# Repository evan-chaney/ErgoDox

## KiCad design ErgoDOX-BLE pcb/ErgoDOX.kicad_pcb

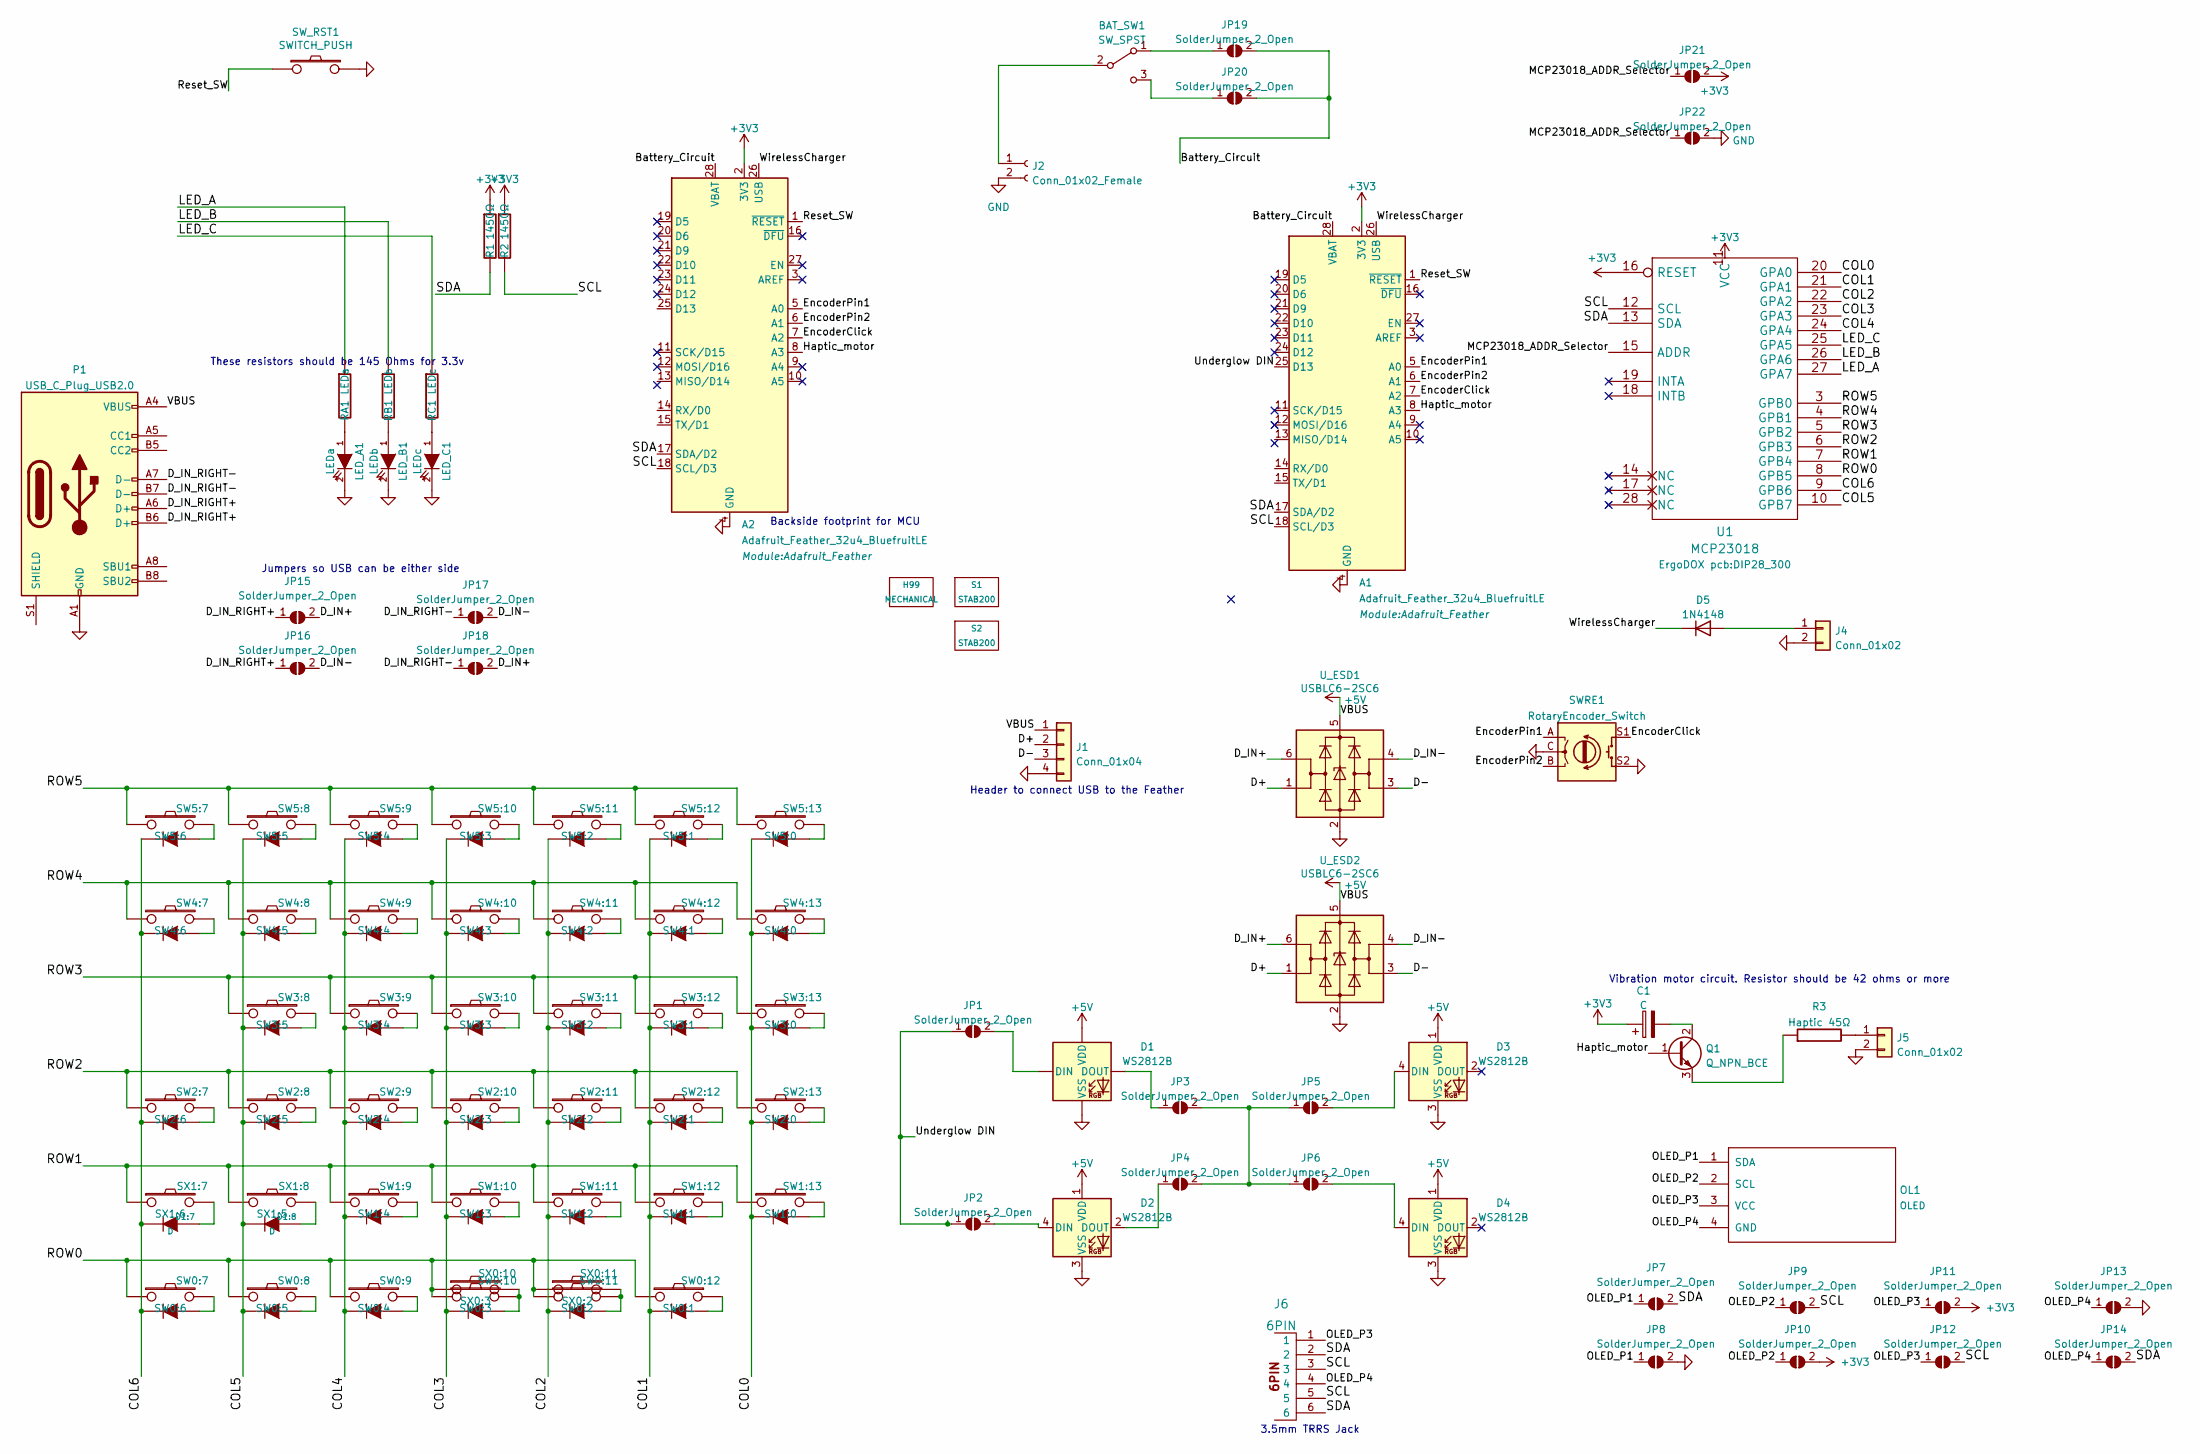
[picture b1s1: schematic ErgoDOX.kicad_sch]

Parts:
A1, A2: Adafruit_Feather_32u4_BluefruitLE; Adafruit_Feather
BAT_SW1: SW_SPST; SW_Slide_1P2T_CK_OS102011MS2Q
C1: C; CP_Radial_Tantal_D5.0mm_P5.00mm
D1, D2, D3, D4: WS2812B; LED_WS2812B_PLCC4_5.0x5.0mm_P3.2mm
D1:7, D1:8: D
D5: 1N4148; D_DO-35_SOD27_P7.62mm_Horizontal
H99: MECHANICAL
J1: Conn_01x04; PinHeader_1x04_P1.00mm_Vertical
J2: Conn_01x02_Female; JST_EH_B2B-EH-A_1x02_P2.50mm_Vertical
J4, J5: Conn_01x02; PinHeader_1x02_P2.00mm_Vertical
J6: 6PIN; 4pin35mmAudio
JP1, JP2, JP3, JP4, JP5, JP6, JP7, JP8, JP9, JP10, JP11, JP12, JP13, JP14, JP15, JP16, JP17, JP18, JP19, JP20, JP21, JP22: SolderJumper_2_Open; SolderJumper-2_P1.3mm_Open_RoundedPad1.0x1.5mm
LED_A1: LEDa
LED_B1: LEDb
LED_C1: LEDc
OL1: OLED; PinHeader_1x04_P2.54mm_Vertical
P1: USB_C_Plug_USB2.0; USB_C_Receptacle_GCT_USB4085
Q1: Q_NPN_BCE; SOT-23
R1, R2: 1450Ω; RESISTOR
R3: Haptic 45Ω; RESISTOR
RA1: LEDa; RESISTOR
RB1: LEDb; RESISTOR
RC1: LEDc; RESISTOR
S1, S2: STAB200
SW0:7: SW0:6; MX_FLIP_DIODE_HOTSWAP
SW0:8: SW0:5; MX_FLIP_DIODE_HOTSWAP
SW0:9: SW0:4; MX_FLIP_DIODE_HOTSWAP
SW0:10: SW0:3; MX_FLIP_DIODE_HOTSWAP
SW0:11: SW0:2; MX_FLIP_DIODE_HOTSWAP
SW0:12: SW0:1; MX_FLIP_DIODE_HOTSWAP
SW1:9: SW1:4; MX_FLIP_DIODE_HOTSWAP
SW1:10: SW1:3; MX_FLIP_DIODE_HOTSWAP
SW1:11: SW1:2; MX_FLIP_DIODE_HOTSWAP
SW1:12: SW1:1; MX_FLIP_DIODE_HOTSWAP
SW1:13: SW1:0; MX_FLIP_DIODE_HOTSWAP
SW2:7: SW2:6; MX_FLIP_DIODE_HOTSWAP
SW2:8: SW2:5; MX_FLIP_DIODE_HOTSWAP
SW2:9: SW2:4; MX_FLIP_DIODE_HOTSWAP
SW2:10: SW2:3; MX_FLIP_DIODE_HOTSWAP
SW2:11: SW2:2; MX_FLIP_DIODE_HOTSWAP
SW2:12: SW2:1; MX_FLIP_DIODE_HOTSWAP
SW2:13: SW2:0; MX_FLIP_DIODE_HOTSWAP
SW3:8: SW3:5; MX_FLIP_DIODE_HOTSWAP
SW3:9: SW3:4; MX_FLIP_DIODE_HOTSWAP
SW3:10: SW3:3; MX_FLIP_DIODE_HOTSWAP
SW3:11: SW3:2; MX_FLIP_DIODE_HOTSWAP
SW3:12: SW3:1; MX_FLIP_DIODE_HOTSWAP
SW3:13: SW3:0; MX_FLIP_DIODE_HOTSWAP
SW4:7: SW4:6; MX_FLIP_DIODE_HOTSWAP
SW4:8: SW4:5; MX_FLIP_DIODE_HOTSWAP
SW4:9: SW4:4; MX_FLIP_DIODE_HOTSWAP
SW4:10: SW4:3; MX_FLIP_DIODE_HOTSWAP
SW4:11: SW4:2; MX_FLIP_DIODE_HOTSWAP
SW4:12: SW4:1; MX_FLIP_DIODE_HOTSWAP
SW4:13: SW4:0; MX_FLIP_DIODE_HOTSWAP
SW5:7: SW5:6; MX_FLIP_DIODE_HOTSWAP
SW5:8: SW5:5; MX_FLIP_DIODE_HOTSWAP
SW5:9: SW5:4; MX_FLIP_DIODE_HOTSWAP
SW5:10: SW5:3; MX_FLIP_DIODE_HOTSWAP
SW5:11: SW5:2; MX_FLIP_DIODE_HOTSWAP
SW5:12: SW5:1; MX_FLIP_DIODE_HOTSWAP
SW5:13: SW5:0; MX_FLIP_DIODE_HOTSWAP
SWRE1: RotaryEncoder_Switch; RotaryEncoder_Alps_EC11E-Switch_Vertical_H20mm
SW_RST1: SWITCH_PUSH; SW_Tactile_SPST_Angled_PTS645Vx39-2LFS
SX0:10: SX0:3
SX0:11: SX0:2
SX1:7: SX1:6
SX1:8: SX1:5
U1: MCP23018; DIP28_300
U_ESD1, U_ESD2: USBLC6-2SC6; SOT-23-6

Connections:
+3V3: A1.2 (3V3), A2.2 (3V3), C1.1, JP10.2 (B), JP11.2 (B), JP21.2 (B), R1.1, R2.1, U1.11 (VCC), U1.16 (RESET)
+5V: D1.1 (VDD), D2.1 (VDD), D3.1 (VDD), D4.1 (VDD), J1.1, P1.A4 (VBUS), P1.A9 (VBUS), P1.B4 (VBUS), P1.B9 (VBUS), U_ESD1.5 (VBUS), U_ESD2.5 (VBUS)
/Battery_Circuit: A1.28 (VBAT), A2.28 (VBAT), JP19.2 (B), JP20.2 (B)
/COL0: SW1:13.4 (K), SW2:13.4 (K), SW3:13.4 (K), SW4:13.4 (K), SW5:13.4 (K), U1.20 (GPA0)
/COL1: SW0:12.4 (K), SW1:12.4 (K), SW2:12.4 (K), SW3:12.4 (K), SW4:12.4 (K), SW5:12.4 (K), U1.21 (GPA1)
/COL2: SW0:11.4 (K), SW1:11.4 (K), SW2:11.4 (K), SW3:11.4 (K), SW4:11.4 (K), SW5:11.4 (K), U1.22 (GPA2)
/COL3: SW0:10.4 (K), SW1:10.4 (K), SW2:10.4 (K), SW3:10.4 (K), SW4:10.4 (K), SW5:10.4 (K), U1.23 (GPA3)
/COL4: SW0:9.4 (K), SW1:9.4 (K), SW2:9.4 (K), SW3:9.4 (K), SW4:9.4 (K), SW5:9.4 (K), U1.24 (GPA4)
/COL5: D1:8.2 (K), SW0:8.4 (K), SW2:8.4 (K), SW3:8.4 (K), SW4:8.4 (K), SW5:8.4 (K), U1.10 (GPB7)
/COL6: D1:7.2 (K), SW0:7.4 (K), SW2:7.4 (K), SW4:7.4 (K), SW5:7.4 (K), U1.9 (GPB6)
/D+: J1.2, U_ESD1.1 (I/O1), U_ESD2.1 (I/O1)
/D-: J1.3, U_ESD1.3 (I/O2), U_ESD2.3 (I/O2)
/D_IN+: JP15.2 (B), JP18.2 (B), U_ESD1.6 (I/O1), U_ESD2.6 (I/O1)
/D_IN-: JP16.2 (B), JP17.2 (B), U_ESD1.4 (I/O2), U_ESD2.4 (I/O2)
/D_IN_RIGHT+: JP15.1 (A), JP16.1 (A), P1.A6 (D+), P1.B6 (D+)
/D_IN_RIGHT-: JP17.1 (A), JP18.1 (A), P1.A7 (D-), P1.B7 (D-)
/EncoderClick: A1.7 (A2), A2.7 (A2), SWRE1.S1
/EncoderPin1: A1.5 (A0), A2.5 (A0), SWRE1.A
/EncoderPin2: A1.6 (A1), A2.6 (A1), SWRE1.B
/Haptic_motor: A1.8 (A3), A2.8 (A3), Q1.1 (B)
/LED_A: RA1.1, U1.27 (GPA7)
/LED_B: RB1.1, U1.26 (GPA6)
/LED_C: RC1.1, U1.25 (GPA5)
/MCP23018_ADDR_Selector: JP21.1 (A), JP22.1 (A), U1.15 (ADDR)
/OLED_P1: JP7.1 (A), JP8.1 (A), OL1.1 (SDA)
/OLED_P2: JP9.1 (A), JP10.1 (A), OL1.2 (SCL)
/OLED_P3: J6.1, JP11.1 (A), JP12.1 (A), OL1.3 (VCC)
/OLED_P4: J6.4, JP13.1 (A), JP14.1 (A), OL1.4 (GND)
/ROW0: SW0:7.1, SW0:8.1, SW0:9.1, SW0:10.1, SW0:11.1, SW0:12.1, SX0:10.1, SX0:11.1, U1.8 (GPB5)
/ROW1: SW1:9.1, SW1:10.1, SW1:11.1, SW1:12.1, SW1:13.1, SX1:7.1, SX1:8.1, U1.7 (GPB4)
/ROW2: SW2:7.1, SW2:8.1, SW2:9.1, SW2:10.1, SW2:11.1, SW2:12.1, SW2:13.1, U1.6 (GPB3)
/ROW3: SW3:8.1, SW3:9.1, SW3:10.1, SW3:11.1, SW3:12.1, SW3:13.1, U1.5 (GPB2)
/ROW4: SW4:7.1, SW4:8.1, SW4:9.1, SW4:10.1, SW4:11.1, SW4:12.1, SW4:13.1, U1.4 (GPB1)
/ROW5: SW5:7.1, SW5:8.1, SW5:9.1, SW5:10.1, SW5:11.1, SW5:12.1, SW5:13.1, U1.3 (GPB0)
/Reset_SW: A1.1 (~RESET), A2.1 (~RESET), SW_RST1.1
/SCL: A1.18 (SCL/D3), A2.18 (SCL/D3), J6.3, J6.5, JP9.2 (B), JP12.2 (B), R2.2, U1.12 (SCL)
/SDA: A1.17 (SDA/D2), A2.17 (SDA/D2), J6.2, J6.6, JP7.2 (B), JP14.2 (B), R1.2, U1.13 (SDA)
/Underglow DIN: A1.25 (D13), JP1.1 (A), JP2.1 (A)
/WirelessCharger: A1.26 (USB), A2.26 (USB), D5.1 (K)
GND: A1.4 (GND), A2.4 (GND), D1.3 (VSS), D2.3 (VSS), D3.3 (VSS), D4.3 (VSS), J1.4, J2.2, J4.2, J5.2, JP8.2 (B), JP13.2 (B), JP22.2 (B), LED_A1.2 (K), LED_B1.2 (K), LED_C1.2 (K), P1.A1 (GND), P1.A12 (GND), P1.B1 (GND), P1.B12 (GND), SWRE1.C, SWRE1.S2, SW_RST1.2, U1.1 (GND), U_ESD1.2 (GND), U_ESD2.2 (GND); also elsewhere on the board
unnamed: BAT_SW1.1 (A), JP19.1 (A)
unnamed: BAT_SW1.2 (B), J2.1
unnamed: BAT_SW1.3 (C), JP20.1 (A)
unnamed: C1.2, Q1.2 (C)
unnamed: D1.2 (DOUT), JP3.1 (A)
unnamed: D1.4 (DIN), JP1.2 (B)
unnamed: D1:7.1 (A), SX1:7.2
unnamed: D1:8.1 (A), SX1:8.2
unnamed: D2.2 (DOUT), JP4.1 (A)
unnamed: D2.4 (DIN), JP2.2 (B)
unnamed: D3.4 (DIN), JP5.2 (B)
unnamed: D4.4 (DIN), JP6.2 (B)
unnamed: D5.2 (A), J4.1
unnamed: J5.1, R3.2
unnamed: JP3.2 (B), JP4.2 (B), JP5.1 (A), JP6.1 (A)
unnamed: LED_A1.1 (A), RA1.2
unnamed: LED_B1.1 (A), RB1.2
unnamed: LED_C1.1 (A), RC1.2
unnamed: Q1.3 (E), R3.1
unnamed: SW0:7.2, SW0:7.3 (A)
unnamed: SW0:8.2, SW0:8.3 (A)
unnamed: SW0:9.2, SW0:9.3 (A)
unnamed: SW0:10.2, SW0:10.3 (A), SX0:10.2
unnamed: SW0:11.2, SW0:11.3 (A), SX0:11.2
unnamed: SW0:12.2, SW0:12.3 (A)
unnamed: SW1:9.2, SW1:9.3 (A)
unnamed: SW1:10.2, SW1:10.3 (A)
unnamed: SW1:11.2, SW1:11.3 (A)
unnamed: SW1:12.2, SW1:12.3 (A)
unnamed: SW1:13.2, SW1:13.3 (A)
unnamed: SW2:7.2, SW2:7.3 (A)
unnamed: SW2:8.2, SW2:8.3 (A)
unnamed: SW2:9.2, SW2:9.3 (A)
unnamed: SW2:10.2, SW2:10.3 (A)
unnamed: SW2:11.2, SW2:11.3 (A)
unnamed: SW2:12.2, SW2:12.3 (A)
unnamed: SW2:13.2, SW2:13.3 (A)
unnamed: SW3:8.2, SW3:8.3 (A)
unnamed: SW3:9.2, SW3:9.3 (A)
unnamed: SW3:10.2, SW3:10.3 (A)
unnamed: SW3:11.2, SW3:11.3 (A)
unnamed: SW3:12.2, SW3:12.3 (A)
unnamed: SW3:13.2, SW3:13.3 (A)
unnamed: SW4:7.2, SW4:7.3 (A)
unnamed: SW4:8.2, SW4:8.3 (A)
unnamed: SW4:9.2, SW4:9.3 (A)
unnamed: SW4:10.2, SW4:10.3 (A)
unnamed: SW4:11.2, SW4:11.3 (A)
unnamed: SW4:12.2, SW4:12.3 (A)
unnamed: SW4:13.2, SW4:13.3 (A)
unnamed: SW5:7.2, SW5:7.3 (A)
unnamed: SW5:8.2, SW5:8.3 (A)
unnamed: SW5:9.2, SW5:9.3 (A)
unnamed: SW5:10.2, SW5:10.3 (A)
unnamed: SW5:11.2, SW5:11.3 (A)
unnamed: SW5:12.2, SW5:12.3 (A)
unnamed: SW5:13.2, SW5:13.3 (A)

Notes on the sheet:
These resistors should be 145 Ohms for 3.3v
Header to connect USB to the Feather
3.5mm TRRS Jack
Vibration motor circuit. Resistor should be 42 ohms or more
Jumpers so USB can be either side
Backside footprint for MCU

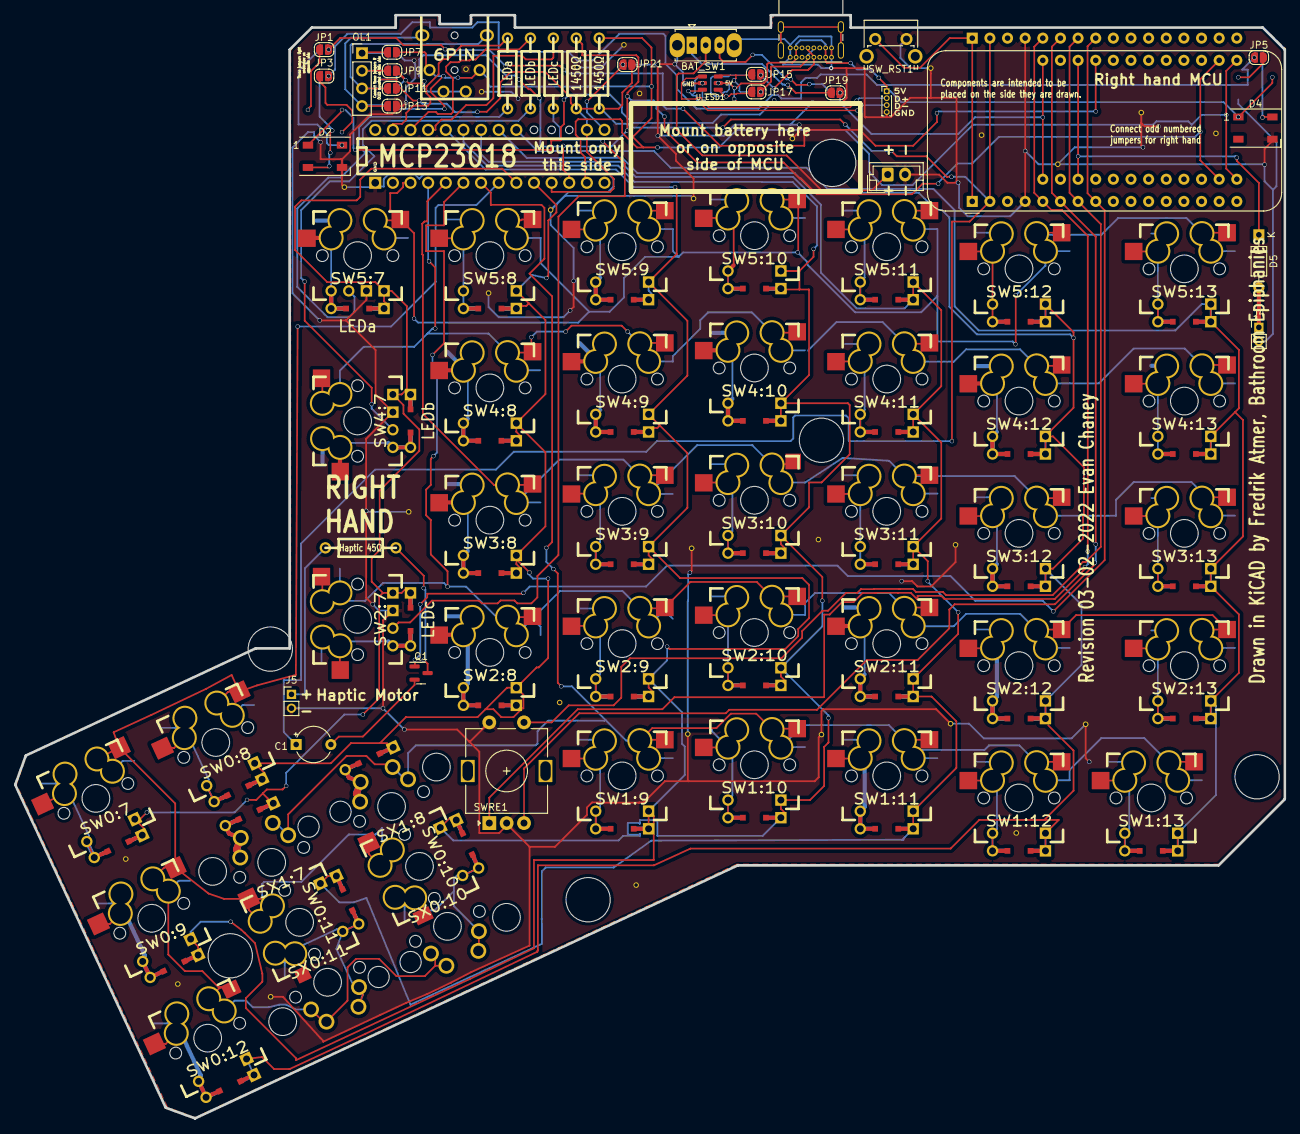
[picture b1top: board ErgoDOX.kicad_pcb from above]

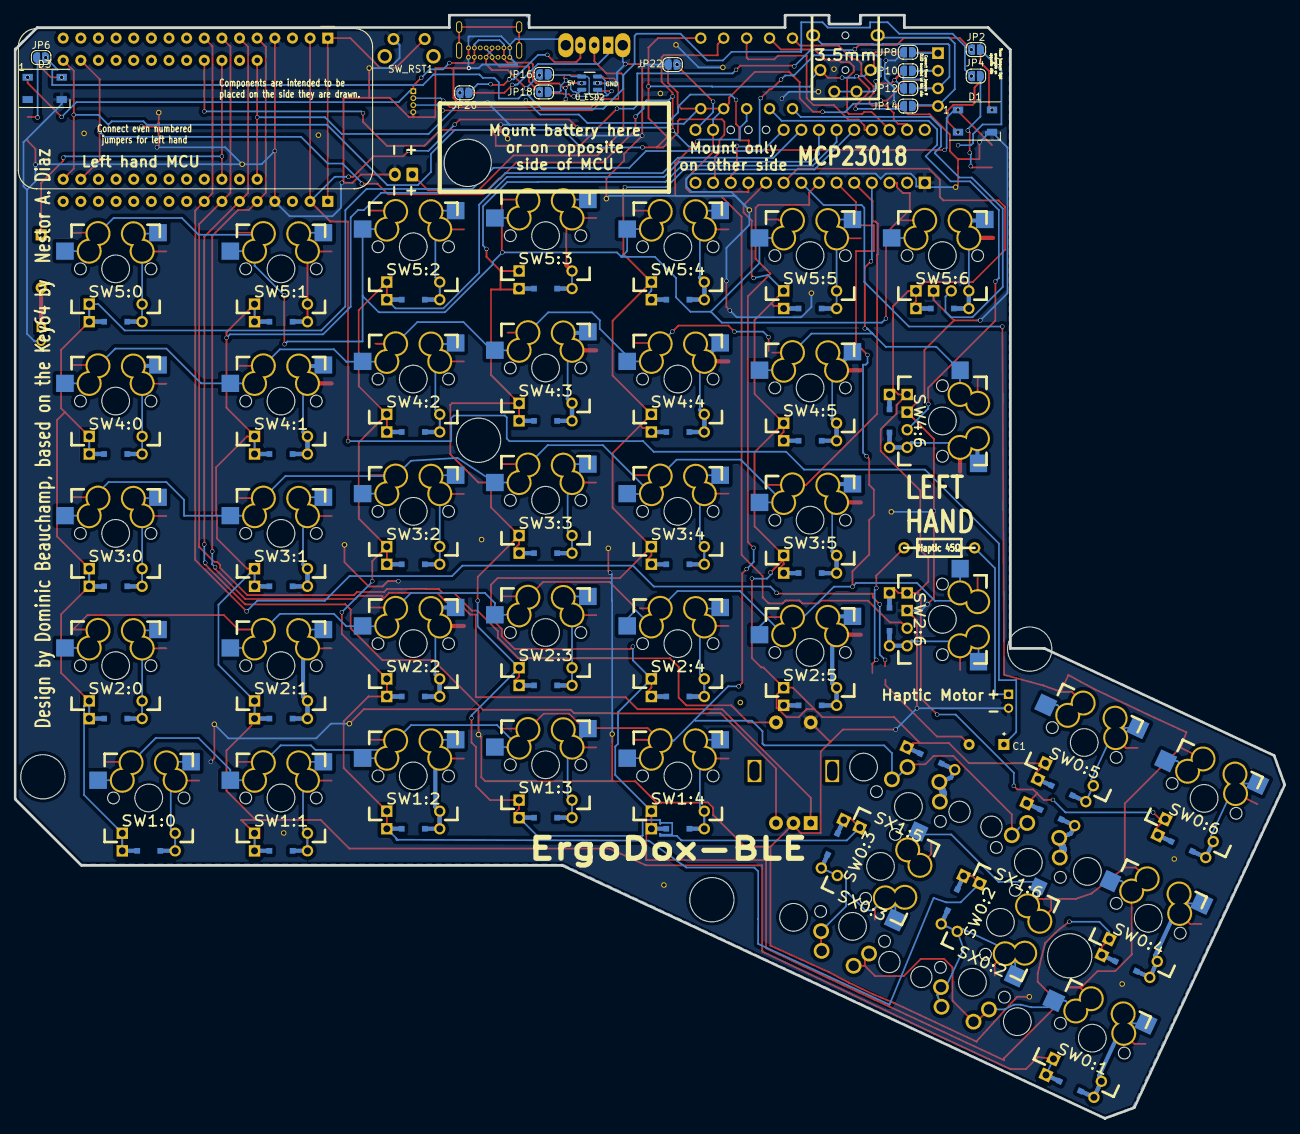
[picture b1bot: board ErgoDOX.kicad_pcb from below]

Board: 2 copper layers, 182.8 x 158.9 mm, 112 parts (15 on the bottom side), 97 nets.

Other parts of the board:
STITCHING_VIA: STITCHING_VIA
STITCHING_VIA#2, STITCHING_VIA#3, STITCHING_VIA#4, STITCHING_VIA#5, STITCHING_VIA#6, STITCHING_VIA#7, STITCHING_VIA#8, STITCHING_VIA#9, STITCHING_VIA#10, STITCHING_VIA#11, STITCHING_VIA#12: STITCHING_VIA
U3: C0720B001F; Battery_CR1225

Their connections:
GND: STITCHING_VIA.GND, STITCHING_VIA#2.GND, STITCHING_VIA#3.GND, STITCHING_VIA#4.GND, STITCHING_VIA#6.GND, STITCHING_VIA#7.GND, STITCHING_VIA#8.GND, STITCHING_VIA#9.GND, STITCHING_VIA#10.GND, STITCHING_VIA#11.GND, STITCHING_VIA#12.GND; also elsewhere on the board

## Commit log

2022-02-03 Split BLE PCB into it's own kicad project
2022-02-03 Begin work on BLE version
    Upgrade Kicad file version
2022-02-04 Slowly try to replace the teensy
2022-02-05 Add some LEDs?
2022-02-07 Add OLED, rotary encoder, vibration motor to schematic
2022-02-08 add notes
2022-02-11 Export footprint from existing ergodox design for the mcp20318
2022-02-11 Add a ton of tracks
2022-02-14 Combine SDAS and SDAM to SDA net
2022-02-15 Make room for battery?
2022-02-15 Link SDA/SCLs
2022-02-16 work on USB
2022-02-16 Connect DIN for LEDs
2022-02-17 Add lots of tracking
2022-02-21 Started adding components to the other side
2022-02-22 Working on jumpers for OLED
2022-02-22 Export new gerbers
2022-02-22 Complete thumb cluster routing
2022-02-23 Do some work on the USB C -> ESD setup
2022-02-23 Add pads for USB and additional jumper for underglow
2022-02-24 Try and add footprint for back side MCU
2022-02-25 Jumper madness
2022-02-26 Stub out charging circuit
2022-02-26 Wire up some jumpers
2022-02-27 USB jumpers and comments
2022-02-28 Battery power switch!
2022-03-02 Add jumpers for battery switch
2022-03-02 Light cleanup
2022-03-03 all sorts of silkscreen work
2022-03-03 Silkscreen work
2022-03-05 add ESD on back side
2022-03-22 Change board tolerances and re-export gerbers
2022-03-22 Add capacitor to haptic motor
2022-03-28 change capacitor to a polarized cap
2022-03-28 Start working on hotswap footprint
2022-03-29 tons of work on hotswap footprint
2022-03-29 Change the other holes to mech/drill
2022-03-29 Set some switches to the new hotswap switch footprint
2022-03-29 Switch most of the rest of switches to the hotswap footprint
2022-03-29 Start cleaning up this mess
2022-03-30 Struggle through reconnecting these
2022-04-05 Reduce track size, begin sorting through the mess
2022-04-06 Add transistor to haptic feedback curcuit
2022-04-07 Make the pads for kailh hot swaps the correct side
2022-12-29 Restart my routing mess
2022-12-29 More routing
2022-12-30 More routing forever
2022-12-30 Split out new footprint for the FLIP_XX hotswap
2022-12-30 Change edge switches to use the same footprint as the main ones and redo routes
2022-12-30 Re-gen gerbers
2022-12-30 Connect a missing trace
2022-12-30 Route me daddy
2022-12-30 Everything is connected
2022-12-30 Rule checking woohoo
2022-12-30 Start adding audio port
2022-12-31 Add some holes and route around them!
2022-12-31 a touch more routing
2022-12-31 Do initial placement of TRRS jack
2022-12-31 Added audio jack and traces
2022-12-31 Fixing some of the clearance issues
2023-01-01 Add jumpers for setting address of IO expander
2023-01-02 Begin playing around with replacing the 23018 with a 23017
2023-01-02 A lot of footprint work
2023-01-02 Routing everything
2023-01-03 Move my bank of resistors because they overlapped with another footprint
2023-01-03 Ground fills for everyone
2023-01-03 Fixing overlapping footprints
2023-01-03 Generate new gerbers
2023-01-04 Adding a bunch of part numbers and verifying sizing
2023-01-05 Remove PCB to MCU JST connector, add mech hole for battery cable
2023-01-05 Tons of back silkscreen work
2023-01-05 Add capacitor
2023-01-09 Add jumpers to fix TRRS
2023-01-10 Build out charging circuit
2023-01-10 Add 3v3 regulator
2023-01-10 Footprints for part of regulator circuit
2023-01-11 Routing my days away
2023-01-11 More routing of encoder
2023-01-11 Finish routing LED resistors
2023-01-12 Moving a bunch of stuff to SMD
2023-01-12 Fixing some silk and moving components
2023-01-12 Scoot silk off pad
2023-01-12 Update footprints based on PCB
2023-01-12 Add some data sheets and model numbers
2023-01-12 Silkscreen cleanup
2023-01-12 Regen gerbers
2023-01-29 Start adding notes for corrections
2023-03-28 Add more notes on mistakes
